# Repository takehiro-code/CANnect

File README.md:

# CANnect

Automotive diagnostic application developed as a part of engineering science 2020 capstone group croject. We built the application that diagnoses vehicle performance from On-board diagnostics-II (OBDII) port, and the mobile application displays the performance data with the Bluetooth connection from the hardware module. The dashboard on the mobile app processes the performance data and visualizes it in table, line chart, meter visualization, etc. in real-time. The performance data, which is OBDII parameter IDs (PIDs), includes engine coolant temperature, fuel pressure, engine RPM, vehicle speed, etc.

## System Overview

## Mobile App

We developed the mobile application with Android Studio, using Java and XML.

<div class="row">
  <div class="column">

  </div>
  <div class="column">

  </div>
</div>

## Contributors

- Choong Jin Ng
- Enes Yazici
- Ranjoat Chana
- Win Aung
- Nicholas Lau
- Takehiro Tanaka

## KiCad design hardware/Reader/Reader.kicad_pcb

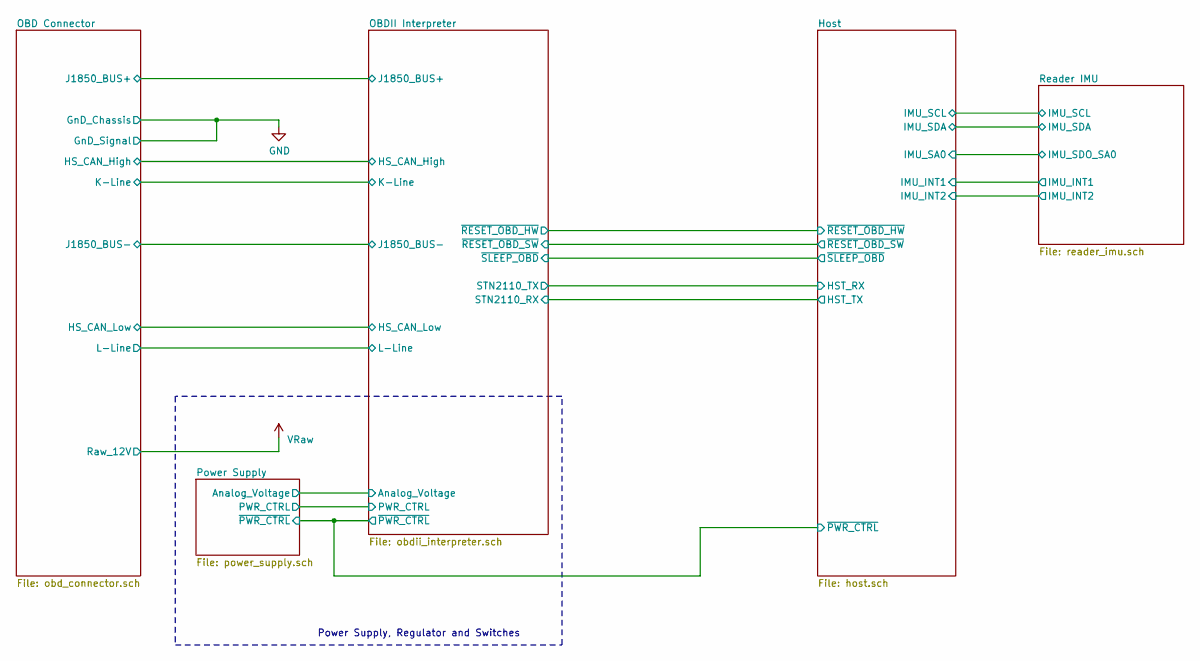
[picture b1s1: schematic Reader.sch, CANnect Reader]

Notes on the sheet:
Power Supply, Regulator and Switches

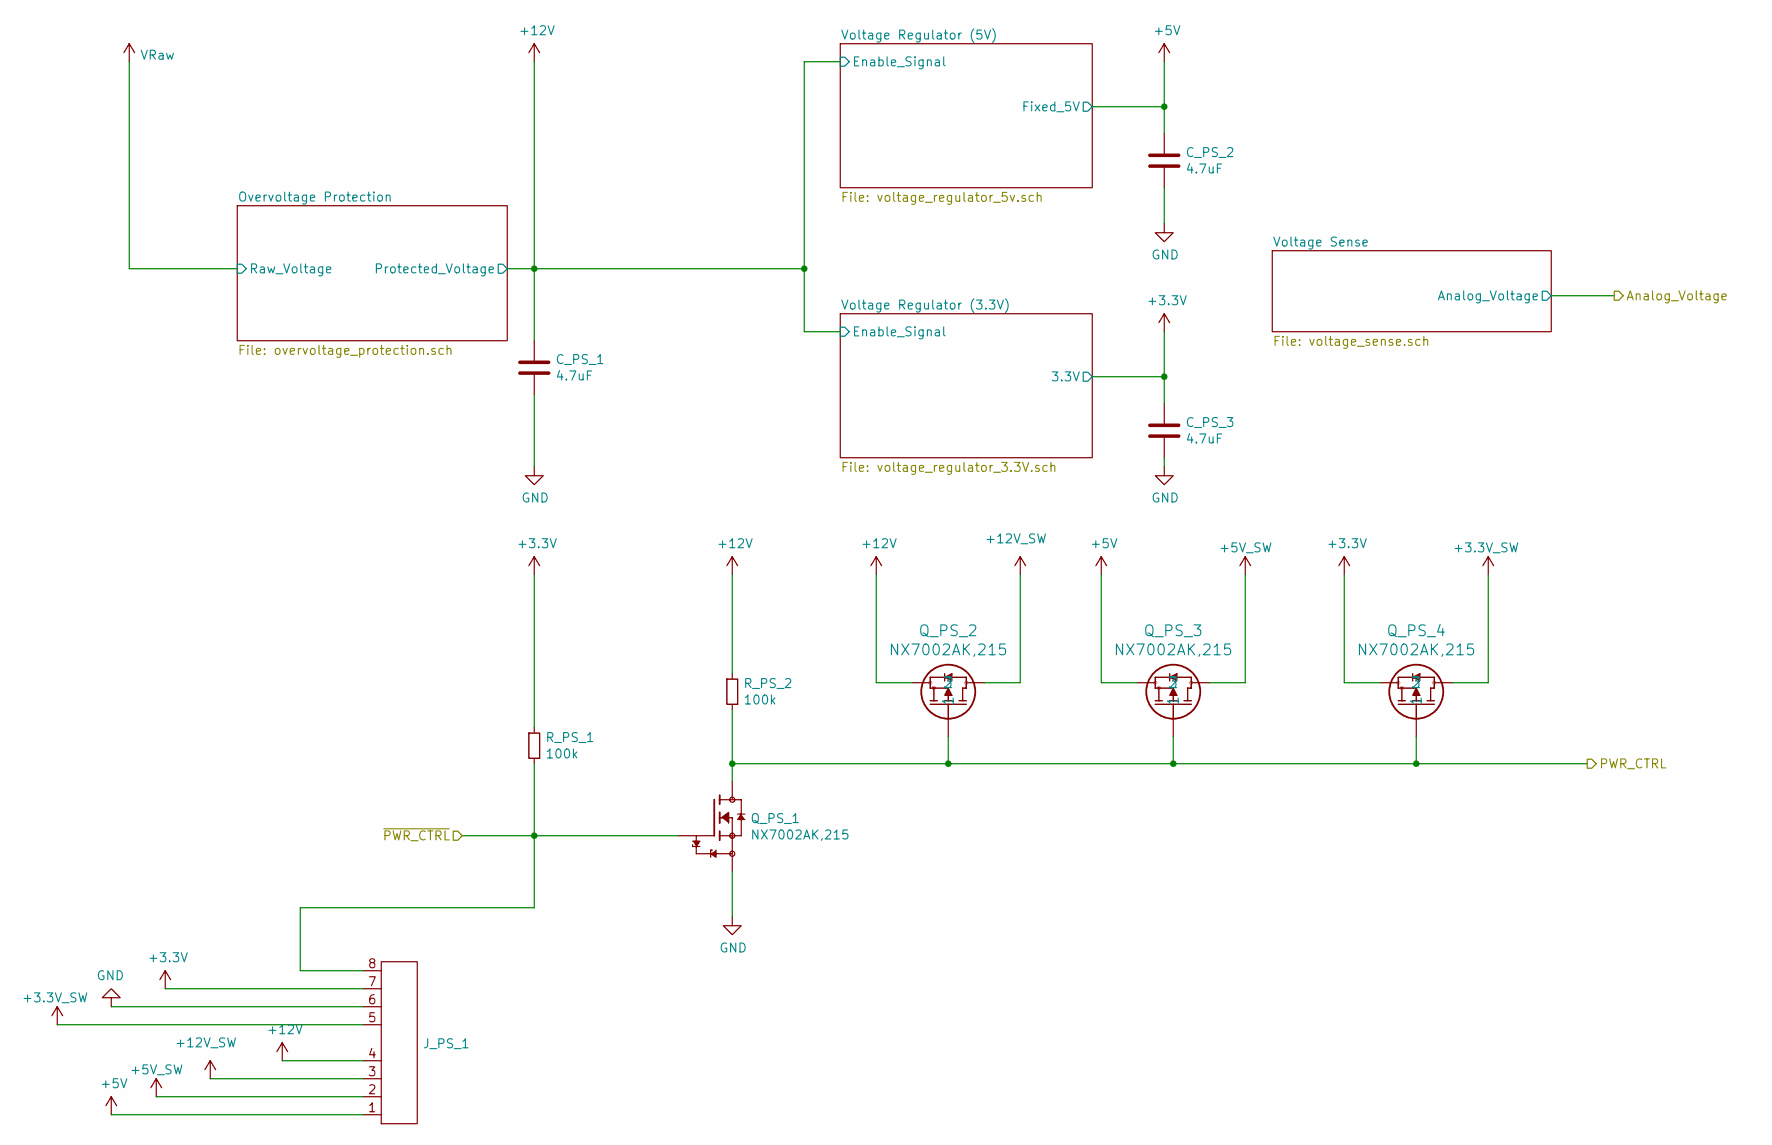
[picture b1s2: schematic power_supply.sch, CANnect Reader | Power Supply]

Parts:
C_PS_1, C_PS_2, C_PS_3: 4.7uF; C1206C475K3RACAUTO; Part Name C1206C475K3RACAUTO; digikeypn 399-7029-1-ND
J_PS_1: Header_Pin_8; PinHeader_1x08_P2.54mm_Vertical
Q_PS_1, Q_PS_2, Q_PS_3, Q_PS_4: NX7002AK,215; SOT95P230X110-3N; Part Name NX7002AK,215; digikeypn 1727-1289-1-ND
R_PS_1, R_PS_2: 100k; RESC1608X55N; Part Name RT0603DRE07100KL; digikeypn 311-2395-1-ND

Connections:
+3.3V_SW: J_PS_1.5, Q_PS_4.2
+3V3: C_PS_3.1, J_PS_1.7, Q_PS_4.3, R_PS_1.1; also elsewhere on the board
+5V: C_PS_2.1, J_PS_1.1, Q_PS_3.3; also elsewhere on the board
+5V_SW: J_PS_1.2, Q_PS_3.2; also elsewhere on the board
+12V_SW: J_PS_1.3, Q_PS_2.2; also elsewhere on the board
/Host/~PWR_CTRL~: J_PS_1.8, Q_PS_1.1, R_PS_1.2; also elsewhere on the board
/OBDII Interpreter/PWR_CTRL: Q_PS_1.3, Q_PS_2.1, Q_PS_3.1, Q_PS_4.1, R_PS_2.2; also elsewhere on the board
Pin4_GnD_Chassis: C_PS_1.2, C_PS_2.2, C_PS_3.2, J_PS_1.6, Q_PS_1.2; also elsewhere on the board

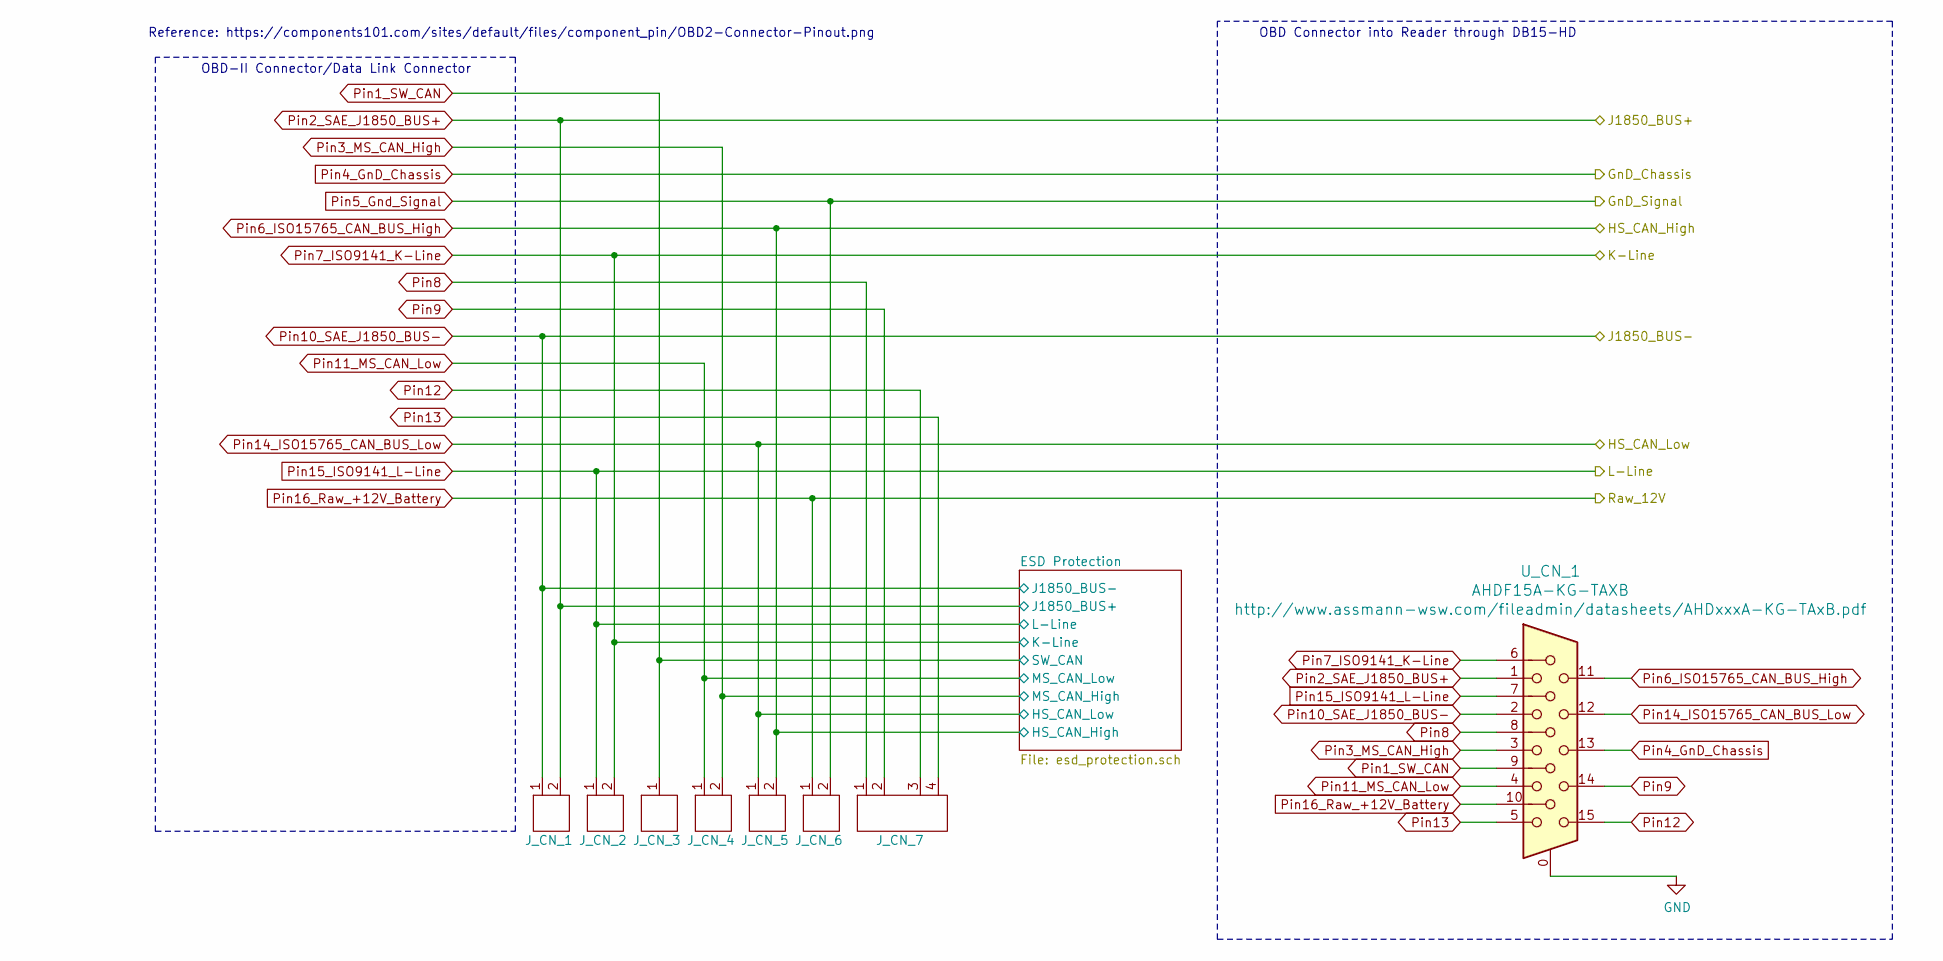
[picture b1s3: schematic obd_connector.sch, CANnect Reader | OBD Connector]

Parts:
J_CN_1, J_CN_2, J_CN_4, J_CN_5, J_CN_6: Header_Pin_2; PinHeader_1x02_P2.54mm_Vertical
J_CN_3: Header_Pin_1; PinHeader_1x01_P2.54mm_Vertical
J_CN_7: Header_Pin_4; PinHeader_1x04_P2.54mm_Vertical
U_CN_1: AHDF15A-KG-TAXB; Part Name AHDF15A-KG-TAXB; digikeypn AE11024-ND

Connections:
Pin1_SW_CAN: J_CN_3.1, U_CN_1.9; also elsewhere on the board
Pin2_SAE_J1850_BUS+: J_CN_1.2, U_CN_1.1; also elsewhere on the board
Pin3_MS_CAN_High: J_CN_4.2, U_CN_1.3; also elsewhere on the board
Pin4_GnD_Chassis: J_CN_6.2, U_CN_1.0, U_CN_1.13; also elsewhere on the board
Pin6_ISO15765_CAN_BUS_High: J_CN_5.2, U_CN_1.11; also elsewhere on the board
Pin7_ISO9141_K-Line: J_CN_2.2, U_CN_1.6; also elsewhere on the board
Pin8: J_CN_7.1, U_CN_1.8
Pin9: J_CN_7.2, U_CN_1.14
Pin10_SAE_J1850_BUS-: J_CN_1.1, U_CN_1.2; also elsewhere on the board
Pin11_MS_CAN_Low: J_CN_4.1, U_CN_1.4; also elsewhere on the board
Pin12: J_CN_7.3, U_CN_1.15
Pin13: J_CN_7.4, U_CN_1.5
Pin14_ISO15765_CAN_BUS_Low: J_CN_5.1, U_CN_1.12; also elsewhere on the board
Pin15_ISO9141_L-Line: J_CN_2.1, U_CN_1.7; also elsewhere on the board

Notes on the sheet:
OBD Connector into Reader through DB15-HD
Reference: https://components101.com/sites/default/files/component_pin/OBD2-Connector-Pinout.png
OBD-II Connector/Data Link Connector

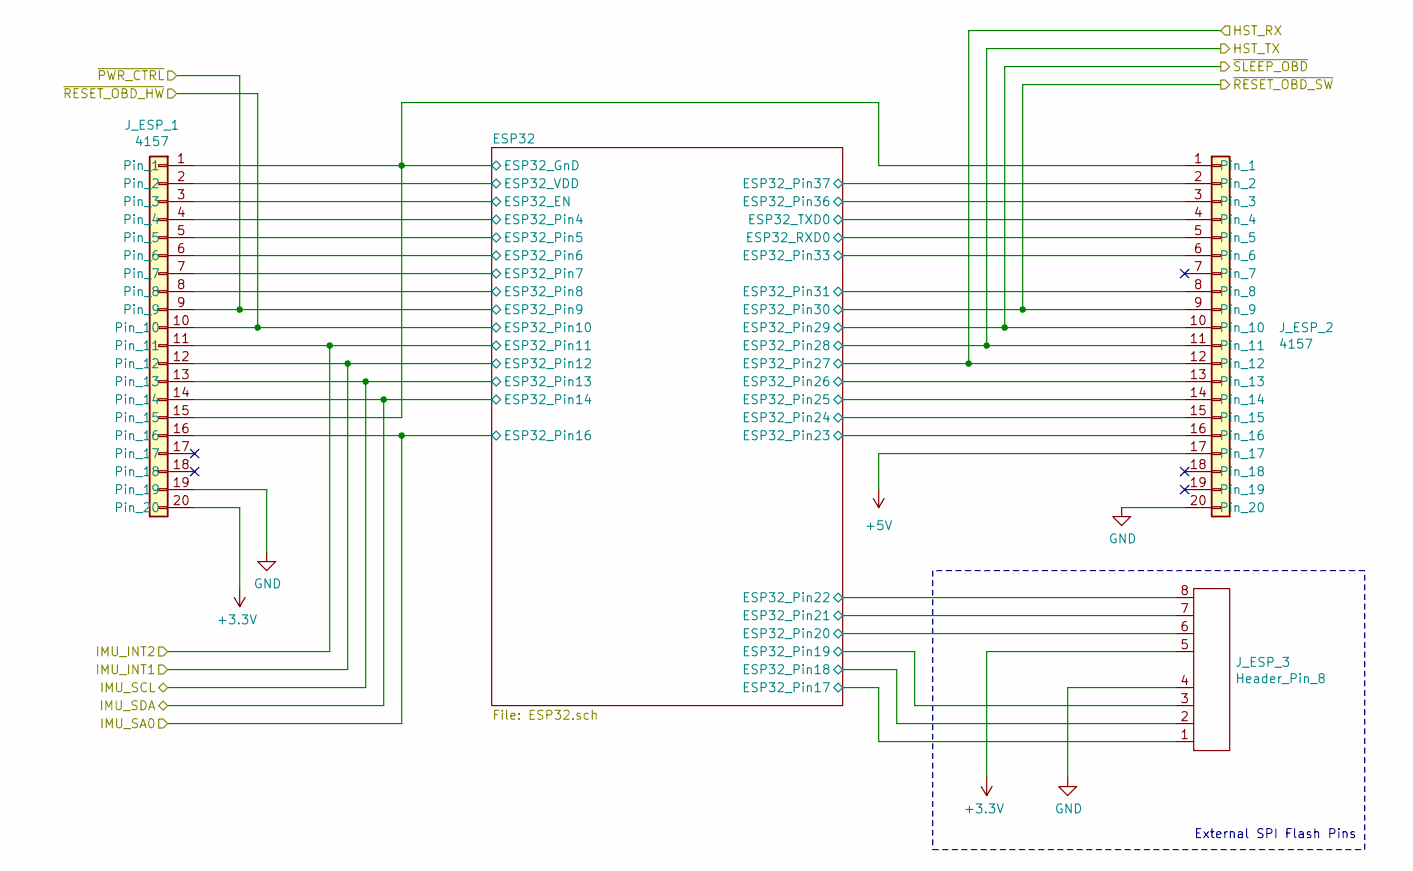
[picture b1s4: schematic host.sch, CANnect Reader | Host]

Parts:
J_ESP_1, J_ESP_2: 4157; PinSocket_1x20_P2.54mm_Vertical; Part Name 4157; digikeypn 1528-2929-ND
J_ESP_3: Header_Pin_8; PinHeader_1x08_P2.54mm_Vertical

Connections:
+3V3: J_ESP_1.2, J_ESP_1.20, J_ESP_3.5; also elsewhere on the board
+5V: J_ESP_2.17; also elsewhere on the board
/Host/ESP32/ESP32_EN: J_ESP_1.3; also elsewhere on the board
/Host/ESP32/ESP32_Pin4: J_ESP_1.4; also elsewhere on the board
/Host/ESP32/ESP32_Pin5: J_ESP_1.5; also elsewhere on the board
/Host/ESP32/ESP32_Pin6: J_ESP_1.6; also elsewhere on the board
/Host/ESP32/ESP32_Pin7: J_ESP_1.7; also elsewhere on the board
/Host/ESP32/ESP32_Pin8: J_ESP_1.8; also elsewhere on the board
/Host/ESP32/ESP32_Pin17: J_ESP_3.1; also elsewhere on the board
/Host/ESP32/ESP32_Pin18: J_ESP_3.2; also elsewhere on the board
/Host/ESP32/ESP32_Pin19: J_ESP_3.3; also elsewhere on the board
/Host/ESP32/ESP32_Pin20: J_ESP_3.6; also elsewhere on the board
/Host/ESP32/ESP32_Pin21: J_ESP_3.7; also elsewhere on the board
/Host/ESP32/ESP32_Pin22: J_ESP_3.8; also elsewhere on the board
/Host/ESP32/ESP32_Pin23: J_ESP_2.16; also elsewhere on the board
/Host/ESP32/ESP32_Pin24: J_ESP_2.15; also elsewhere on the board
/Host/ESP32/ESP32_Pin25: J_ESP_2.14; also elsewhere on the board
/Host/ESP32/ESP32_Pin26: J_ESP_2.13; also elsewhere on the board
/Host/ESP32/ESP32_Pin31: J_ESP_2.8; also elsewhere on the board
/Host/ESP32/ESP32_Pin33: J_ESP_2.6; also elsewhere on the board
/Host/ESP32/ESP32_Pin36: J_ESP_2.3; also elsewhere on the board
/Host/ESP32/ESP32_Pin37: J_ESP_2.2; also elsewhere on the board
/Host/ESP32/ESP32_RXD0: J_ESP_2.5; also elsewhere on the board
/Host/ESP32/ESP32_TXD0: J_ESP_2.4; also elsewhere on the board
/Host/HST_RX: J_ESP_2.12; also elsewhere on the board
/Host/HST_TX: J_ESP_2.11; also elsewhere on the board
/Host/IMU_INT1: J_ESP_1.12; also elsewhere on the board
/Host/IMU_INT2: J_ESP_1.11; also elsewhere on the board
/Host/IMU_SA0: J_ESP_1.16; also elsewhere on the board
/Host/IMU_SCL: J_ESP_1.13; also elsewhere on the board
/Host/IMU_SDA: J_ESP_1.14; also elsewhere on the board
/Host/~PWR_CTRL~: J_ESP_1.9; also elsewhere on the board
/Host/~RESET_OBD_HW~: J_ESP_1.10; also elsewhere on the board
/Host/~RESET_OBD_SW~: J_ESP_2.9; also elsewhere on the board
/Host/~SLEEP_OBD~: J_ESP_2.10; also elsewhere on the board
Pin4_GnD_Chassis: J_ESP_1.1, J_ESP_1.15, J_ESP_1.19, J_ESP_2.1, J_ESP_2.20, J_ESP_3.4; also elsewhere on the board

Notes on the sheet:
External SPI Flash Pins

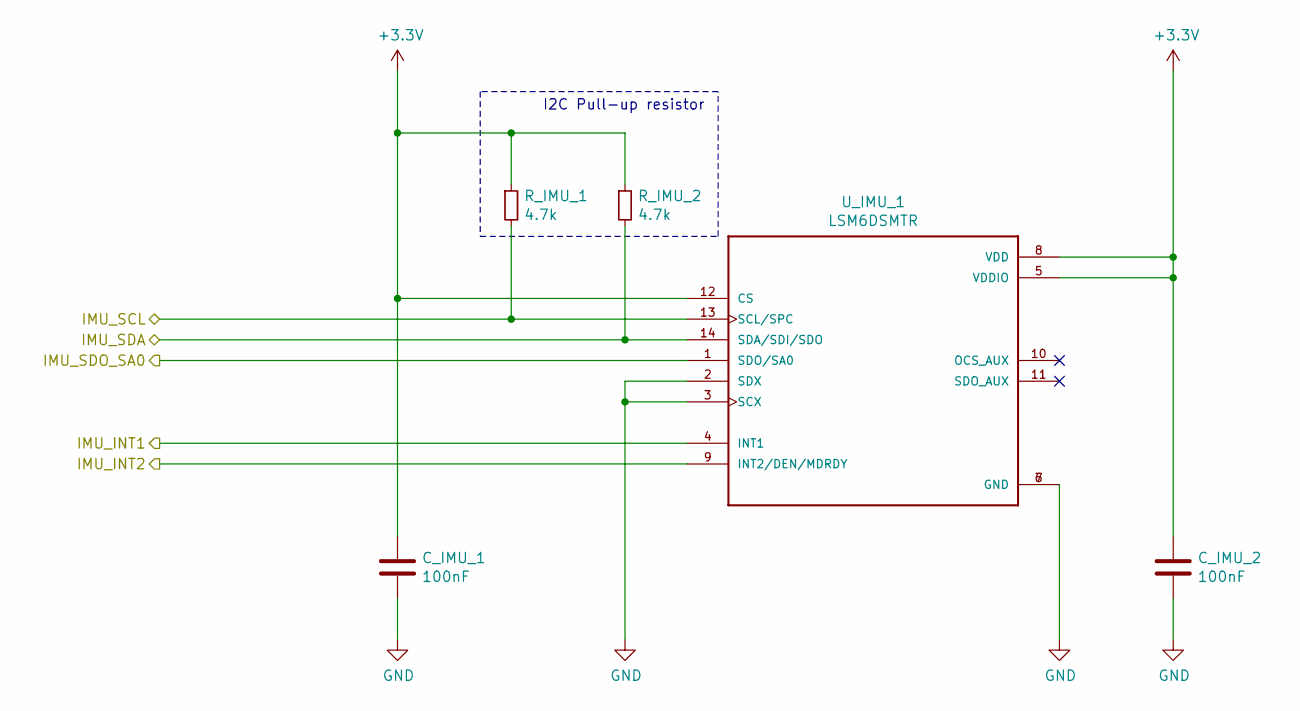
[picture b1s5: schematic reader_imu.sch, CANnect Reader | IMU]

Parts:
C_IMU_1, C_IMU_2: 100nF; CAPC1608X90N; Part Name C1608X7R2A103K080AA; digikeypn 445-1304-1-ND
R_IMU_1, R_IMU_2: 4.7k; RESC1608X55N; Part Name RT0603DRD074K7L; digikeypn 311-4.7KDCT-ND
U_IMU_1: LSM6DSMTR; PQFN50P300X250X86-14N; Part Name LSM6DSMTR; digikeypn 497-16696-1-ND

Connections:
+3V3: C_IMU_1.1, C_IMU_2.1, R_IMU_1.1, R_IMU_2.1, U_IMU_1.5 (VDDIO), U_IMU_1.8 (VDD), U_IMU_1.12 (CS); also elsewhere on the board
/Host/IMU_INT1: U_IMU_1.4 (INT1); also elsewhere on the board
/Host/IMU_INT2: U_IMU_1.9 (INT2/DEN/MDRDY); also elsewhere on the board
/Host/IMU_SA0: U_IMU_1.1 (SDO/SA0); also elsewhere on the board
/Host/IMU_SCL: R_IMU_1.2, U_IMU_1.13 (SCL/SPC); also elsewhere on the board
/Host/IMU_SDA: R_IMU_2.2, U_IMU_1.14 (SDA/SDI/SDO); also elsewhere on the board
Pin4_GnD_Chassis: C_IMU_1.2, C_IMU_2.2, U_IMU_1.2 (SDX), U_IMU_1.3 (SCX), U_IMU_1.6 (GND), U_IMU_1.7 (GND); also elsewhere on the board

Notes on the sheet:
I2C Pull-up resistor

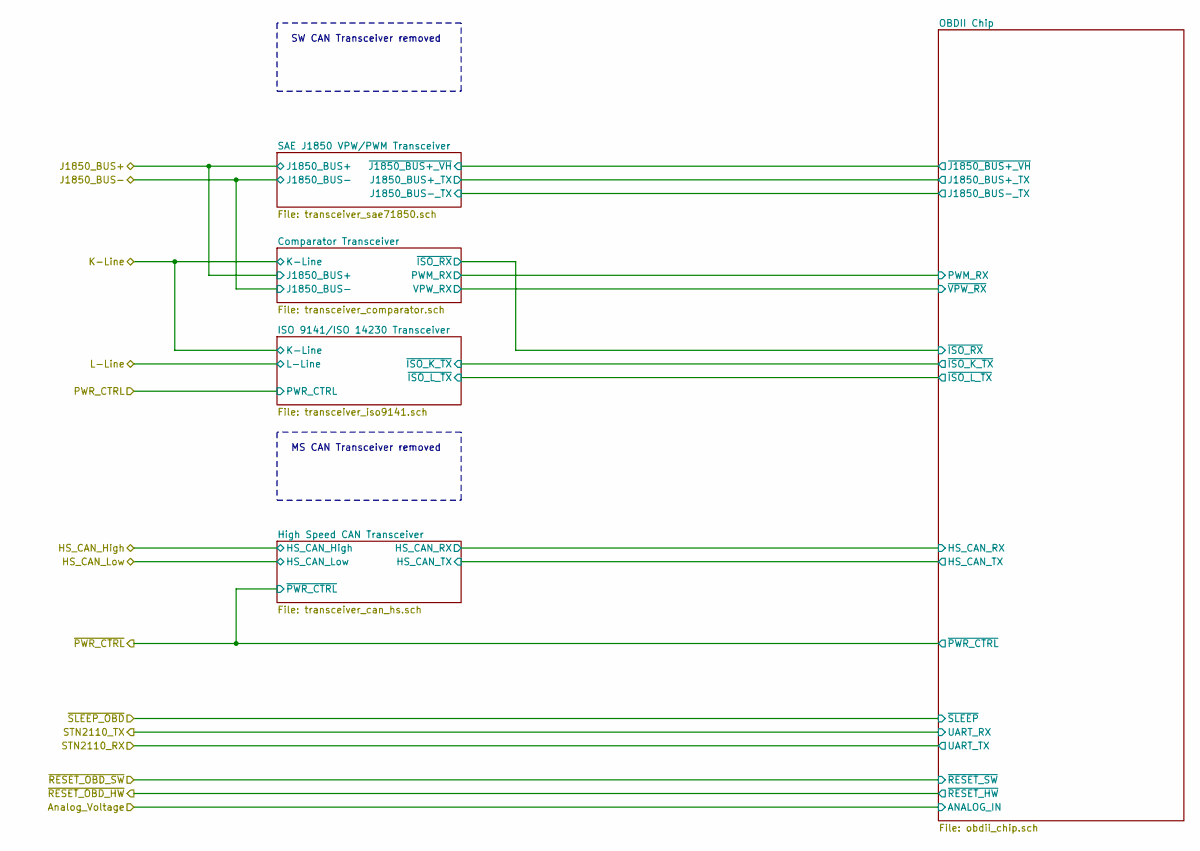
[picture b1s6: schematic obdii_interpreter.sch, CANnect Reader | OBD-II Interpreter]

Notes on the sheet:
SW CAN Transceiver removed
MS CAN Transceiver removed

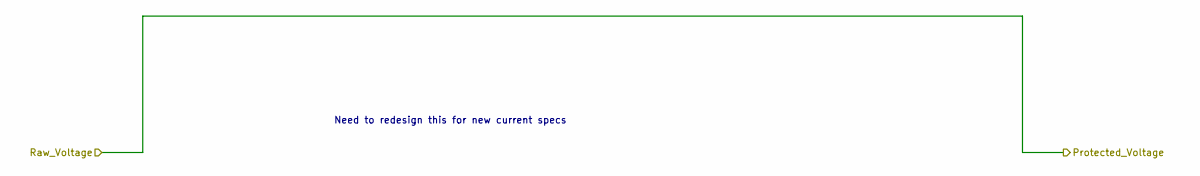
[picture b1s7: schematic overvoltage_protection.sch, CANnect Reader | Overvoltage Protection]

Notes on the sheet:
Need to redesign this for new current specs

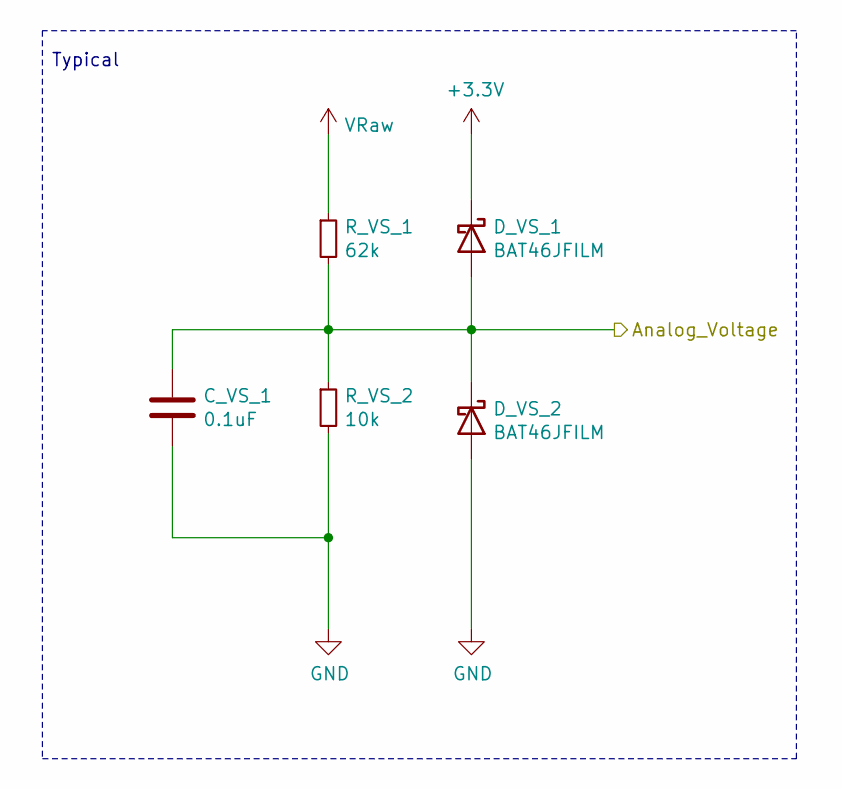
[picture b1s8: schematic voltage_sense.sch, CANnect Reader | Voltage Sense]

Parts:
C_VS_1: 0.1uF; CAPC1608X90; Part Name CC0603JRX7R8BB104; digikeypn 311-1777-1-ND
D_VS_1, D_VS_2: BAT46JFILM; Part Name BAT46JFILM; digikeypn 497-6653-1-ND
R_VS_1: 62k; RESC2012X60N; Part Name RT0805FRE0762KL; digikeypn 13-RT0805FRE0762KLCT-ND
R_VS_2: 10k; RESC1608X55N; Part Name RT0603FRE0710KL; digikeypn YAG2321CT-ND

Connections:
+3V3: D_VS_1.1 (K); also elsewhere on the board
/OBDII Interpreter/Analog_Voltage: C_VS_1.1, D_VS_1.2 (A), D_VS_2.1 (K), R_VS_1.2, R_VS_2.1; also elsewhere on the board
Pin4_GnD_Chassis: C_VS_1.2, D_VS_2.2 (A), R_VS_2.2; also elsewhere on the board

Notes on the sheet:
Typical

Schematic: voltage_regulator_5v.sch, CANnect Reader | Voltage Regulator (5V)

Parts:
C_VR1_1: 4.7uF; C1206C475K3RACAUTO; Part Name C1206C475K3RACAUTO; digikeypn 399-7029-1-ND
C_VR1_2: 0.1uF; CAPC1608X90; Part Name CC0603JRX7R8BB104; digikeypn 311-1777-1-ND
C_VR1_3: 1uF; 0603; Part Name C0603C105K4RACTU; digikeypn 399-7847-1-ND
L_VR1: 4.7uH; CV201210-4R7K; Part Name CV201210-4R7K; digikeypn CV201210-4R7KCT-ND
U_VR1: MAX25276ATCA_VY+; MAX25276ATCA&slash_VY&plus_; Part Name MAX25276ATCA/VY+; digikeypn 175-MAX25276ATCA/VY+-ND

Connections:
+5V: L_VR1.1, U_VR1.9 (OUT); also elsewhere on the board
unnamed: C_VR1_1.2, U_VR1.4 (SUP)
unnamed: C_VR1_2.1, U_VR1.3 (BST)
unnamed: C_VR1_2.2, L_VR1.2, U_VR1.5 (LX)
unnamed: C_VR1_3.1, U_VR1.8 (FB), U_VR1.10 (BIAS)
Pin4_GnD_Chassis: C_VR1_1.1, C_VR1_3.2, U_VR1.6 (PGND), U_VR1.7 (AGND), U_VR1.13 (EPAD); also elsewhere on the board

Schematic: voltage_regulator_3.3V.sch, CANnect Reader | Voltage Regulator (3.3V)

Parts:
C_VR2_1: 4.7uF; C1206C475K3RACAUTO; Part Name C1206C475K3RACAUTO; digikeypn 399-7029-1-ND
C_VR2_2: 0.1uF; CAPC1608X90; Part Name CC0603JRX7R8BB104; digikeypn 311-1777-1-ND
C_VR2_3: 1uF; 0603; Part Name C0603C105K4RACTU; digikeypn 399-7847-1-ND
L_VR2: 4.7uH; CV201210-4R7K; Part Name CV201210-4R7K; digikeypn CV201210-4R7KCT-ND
R_VR2_1, R_VR2_2: 100k; RESC1608X55N; Part Name RT0603DRE07100KL; digikeypn 311-2395-1-ND
R_VR2_3: 115k; RESC1608X55N; Part Name RT0402DRE07115KL; digikeypn 311-2218-1-ND
U_VR2: MAX25276ATCA_VY+; MAX25276ATCA&slash_VY&plus_; Part Name MAX25276ATCA/VY+; digikeypn 175-MAX25276ATCA/VY+-ND

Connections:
+3V3: L_VR2.1, R_VR2_3.1, U_VR2.9 (OUT); also elsewhere on the board
unnamed: C_VR2_1.1, U_VR2.4 (SUP)
unnamed: C_VR2_2.1, U_VR2.3 (BST)
unnamed: C_VR2_2.2, L_VR2.2, U_VR2.5 (LX)
unnamed: C_VR2_3.1, U_VR2.10 (BIAS)
unnamed: R_VR2_1.2, R_VR2_2.1, R_VR2_3.2, U_VR2.8 (FB)
Pin4_GnD_Chassis: C_VR2_1.2, C_VR2_3.2, R_VR2_1.1, R_VR2_2.2, U_VR2.6 (PGND), U_VR2.7 (AGND), U_VR2.13 (EPAD); also elsewhere on the board

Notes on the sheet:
Resistor Divider to convert 5V to 3.3V

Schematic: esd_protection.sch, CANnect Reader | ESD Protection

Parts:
D_ESD_1, D_ESD_2: PESD2CAN,215; SOT95P230X110-3N; Part Name PESD2CAN,215; digikeypn 1727-3891-1-ND
D_ESD_3: MMBZ27VCLFHT116; Part Name MMBZ27VCLFHT116; digikeypn MMBZ27VCLFHT116CT-ND
D_ESD_4, D_ESD_5: MMBZ27VALT3G; SOT95P237X111-3N; Part Name MMBZ27VALT3G; digikeypn MMBZ27VALT3GOSCT-ND

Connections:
Pin1_SW_CAN: D_ESD_3.2; also elsewhere on the board
Pin2_SAE_J1850_BUS+: D_ESD_5.1; also elsewhere on the board
Pin3_MS_CAN_High: D_ESD_2.1; also elsewhere on the board
Pin4_GnD_Chassis: D_ESD_1.3, D_ESD_2.3, D_ESD_3.1, D_ESD_4.3, D_ESD_5.3; also elsewhere on the board
Pin6_ISO15765_CAN_BUS_High: D_ESD_1.1; also elsewhere on the board
Pin7_ISO9141_K-Line: D_ESD_4.1; also elsewhere on the board
Pin10_SAE_J1850_BUS-: D_ESD_5.2; also elsewhere on the board
Pin11_MS_CAN_Low: D_ESD_2.2; also elsewhere on the board
Pin14_ISO15765_CAN_BUS_Low: D_ESD_1.2; also elsewhere on the board
Pin15_ISO9141_L-Line: D_ESD_4.2; also elsewhere on the board

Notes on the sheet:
ESD Protection (IEC61000-4-2 Level 4)

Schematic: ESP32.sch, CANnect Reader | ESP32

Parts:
CP_ESP_1: 100uF; UCB0J101MCL1GS; Part Name UCB0J101MCL1GS; digikeypn 493-9357-1-ND
C_ESP_1, C_ESP_2: 0.1uF; CAPC1608X90; Part Name CC0603JRX7R8BB104; digikeypn 311-1777-1-ND
LED_ESP_1: Bluetooth Status; LED_0603_1608Metric; Part Name 150060VS75000; digikeypn 732-4980-1-ND
R_ESP_1, R_ESP_4: 10k; RESC1608X55N; Part Name RT0603FRE0710KL; digikeypn YAG2321CT-ND
R_ESP_2, R_ESP_3, R_ESP_5: 500; RESC1508X55N; Part Name MCT0603PD4990DP500; digikeypn 749-1523-1-ND
SW_ESP_1, SW_ESP_2: PTS647SK38SMTR2LFS; Part Name PTS 647 SK38 SMTR2 LFS; digikeypn PTS647SK38SMTR2LFSCT-ND
U_ESP_1: ESP32-WROOM-32D; CANtech-ESP32-WROOM-32; Part Name USB4110-GF-A; digikeypn 1965-ESP32-WROOM-32D(4MB)CT-ND

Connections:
+3V3: CP_ESP_1.1, R_ESP_1.1, R_ESP_4.2, U_ESP_1.2 (VDD); also elsewhere on the board
/Host/ESP32/ESP32_EN: C_ESP_1.1, SW_ESP_1.2, U_ESP_1.3 (EN); also elsewhere on the board
/Host/ESP32/ESP32_Pin4: U_ESP_1.4 (SENSOR_VP); also elsewhere on the board
/Host/ESP32/ESP32_Pin5: U_ESP_1.5 (SENSOR_VN); also elsewhere on the board
/Host/ESP32/ESP32_Pin6: U_ESP_1.6 (IO34); also elsewhere on the board
/Host/ESP32/ESP32_Pin7: U_ESP_1.7 (IO35); also elsewhere on the board
/Host/ESP32/ESP32_Pin8: U_ESP_1.8 (IO32); also elsewhere on the board
/Host/ESP32/ESP32_Pin17: U_ESP_1.17 (SHD/SD2); also elsewhere on the board
/Host/ESP32/ESP32_Pin18: U_ESP_1.18 (SWP/SD3); also elsewhere on the board
/Host/ESP32/ESP32_Pin19: U_ESP_1.19 (SCS/CMD); also elsewhere on the board
/Host/ESP32/ESP32_Pin20: U_ESP_1.20 (SCK/CLK); also elsewhere on the board
/Host/ESP32/ESP32_Pin21: U_ESP_1.21 (SDO/SD0); also elsewhere on the board
/Host/ESP32/ESP32_Pin22: U_ESP_1.22 (SDI/SD1); also elsewhere on the board
/Host/ESP32/ESP32_Pin23: U_ESP_1.23 (IO15); also elsewhere on the board
/Host/ESP32/ESP32_Pin24: R_ESP_3.2, U_ESP_1.24 (IO2); also elsewhere on the board
/Host/ESP32/ESP32_Pin25: C_ESP_2.1, SW_ESP_2.3, U_ESP_1.25 (IO0); also elsewhere on the board
/Host/ESP32/ESP32_Pin26: U_ESP_1.26 (IO4); also elsewhere on the board
/Host/ESP32/ESP32_Pin31: U_ESP_1.31 (IO19); also elsewhere on the board
/Host/ESP32/ESP32_Pin33: U_ESP_1.33 (IO21); also elsewhere on the board
/Host/ESP32/ESP32_Pin36: U_ESP_1.36 (IO22); also elsewhere on the board
/Host/ESP32/ESP32_Pin37: U_ESP_1.37 (IO23); also elsewhere on the board
/Host/ESP32/ESP32_RXD0: U_ESP_1.34 (RXD0/IO3); also elsewhere on the board
/Host/ESP32/ESP32_TXD0: U_ESP_1.35 (TXD0/IO1); also elsewhere on the board
/Host/HST_RX: U_ESP_1.27 (IO16); also elsewhere on the board
/Host/HST_TX: U_ESP_1.28 (IO17); also elsewhere on the board
/Host/IMU_INT1: U_ESP_1.12 (IO27); also elsewhere on the board
/Host/IMU_INT2: U_ESP_1.11 (IO26); also elsewhere on the board
/Host/IMU_SA0: U_ESP_1.16 (IO13); also elsewhere on the board
/Host/IMU_SCL: U_ESP_1.13 (IO14); also elsewhere on the board
/Host/IMU_SDA: U_ESP_1.14 (IO12); also elsewhere on the board
/Host/~PWR_CTRL~: U_ESP_1.9 (IO33); also elsewhere on the board
/Host/~RESET_OBD_HW~: U_ESP_1.10 (IO25); also elsewhere on the board
/Host/~RESET_OBD_SW~: U_ESP_1.30 (IO18); also elsewhere on the board
/Host/~SLEEP_OBD~: U_ESP_1.29 (IO5); also elsewhere on the board
unnamed: LED_ESP_1.2 (A), R_ESP_3.1
unnamed: R_ESP_1.2, SW_ESP_1.1
unnamed: R_ESP_2.1, SW_ESP_1.3
unnamed: R_ESP_4.1, SW_ESP_2.2
unnamed: R_ESP_5.2, SW_ESP_2.4
Pin4_GnD_Chassis: CP_ESP_1.2, C_ESP_1.2, C_ESP_2.2, LED_ESP_1.1 (K), R_ESP_2.2, R_ESP_5.1, U_ESP_1.1 (GND), U_ESP_1.15 (GND), U_ESP_1.38 (GND), U_ESP_1.39 (GND); also elsewhere on the board

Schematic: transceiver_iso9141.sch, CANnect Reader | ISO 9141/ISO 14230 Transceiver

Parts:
Q_ISO_1, Q_ISO_2: IRLML5103TRPBF; Part Name IRLML5103TRPBF; digikeypn IRLML5103PBFCT-ND
Q_ISO_3, Q_ISO_4: MMBT3904WT1G; SOT-23; Part Name MMBT3904WT1G; digikeypn MMBT3904WT1GOSCT-ND
R_ISO_1, R_ISO_2: 1k; RC1608F102CS; Part Name RC1608F102CS; digikeypn 1276-3484-1-ND
R_ISO_3, R_ISO_4: 510k; RESC2012X50N; Part Name RR1220P-514-D; digikeypn RR12P510KDCT-ND

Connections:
/OBDII Interpreter/ISO 9141/ISO 14230 Transceiver/~ISO_K_TX~: R_ISO_1.2; also elsewhere on the board
/OBDII Interpreter/ISO 9141/ISO 14230 Transceiver/~ISO_L_TX~: R_ISO_2.2; also elsewhere on the board
/OBDII Interpreter/PWR_CTRL: Q_ISO_1.1, Q_ISO_2.1; also elsewhere on the board
unnamed: Q_ISO_1.2, R_ISO_3.2
unnamed: Q_ISO_2.2, R_ISO_4.2
unnamed: Q_ISO_3.1 (B), R_ISO_1.1
unnamed: Q_ISO_4.1 (B), R_ISO_2.1
Pin4_GnD_Chassis: Q_ISO_3.2 (E), Q_ISO_4.2 (E); also elsewhere on the board
Pin7_ISO9141_K-Line: Q_ISO_3.3 (C), R_ISO_3.1; also elsewhere on the board
Pin15_ISO9141_L-Line: Q_ISO_4.3 (C), R_ISO_4.1; also elsewhere on the board

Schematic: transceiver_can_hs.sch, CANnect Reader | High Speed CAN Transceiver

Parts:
C_HSCAN_1, C_HSCAN_2: 560pF; CAPC1608X90; Part Name CC0603JRX7R9BB561; digikeypn 311-4020-1-ND‎
C_HSCAN_3: 1uF; 0603; Part Name C0603C105K4RACTU; digikeypn 399-7847-1-ND
Q_HSCAN_1: NX7002AK,215; SOT95P230X110-3N; Part Name NX7002AK,215; digikeypn 1727-1289-1-ND
R_HSCAN_1: 100k; RESC1608X55N; Part Name RT0603DRE07100KL; digikeypn 311-2395-1-ND
R_HSCAN_2, R_HSCAN_3: 100; RESC3216X70N; Part Name ERJ-8ENF1000V; digikeypn P100FCT-ND
U_HSCAN_1: MCP2562-H_MF; MCP2562-H&slash_MF; Part Name MCP2562-H_MF; digikeypn MCP2562-H/MF-ND

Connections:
+3V3: R_HSCAN_1.1, U_HSCAN_1.5 (VIO); also elsewhere on the board
+5V: C_HSCAN_3.2, U_HSCAN_1.3 (VDD); also elsewhere on the board
/Host/~PWR_CTRL~: Q_HSCAN_1.1; also elsewhere on the board
/OBDII Interpreter/High Speed CAN Transceiver/HS_CAN_RX: U_HSCAN_1.4 (RXD); also elsewhere on the board
/OBDII Interpreter/High Speed CAN Transceiver/HS_CAN_TX: U_HSCAN_1.1 (TXD); also elsewhere on the board
unnamed: C_HSCAN_1.1, R_HSCAN_2.2
unnamed: C_HSCAN_2.1, R_HSCAN_3.2
unnamed: Q_HSCAN_1.3, R_HSCAN_1.2, U_HSCAN_1.8 (STBY)
Pin4_GnD_Chassis: C_HSCAN_1.2, C_HSCAN_2.2, C_HSCAN_3.1, Q_HSCAN_1.2, U_HSCAN_1.2 (VSS), U_HSCAN_1.9 (EPAD); also elsewhere on the board
Pin6_ISO15765_CAN_BUS_High: R_HSCAN_3.1, U_HSCAN_1.7 (CANH); also elsewhere on the board
Pin14_ISO15765_CAN_BUS_Low: R_HSCAN_2.1, U_HSCAN_1.6 (CANL); also elsewhere on the board

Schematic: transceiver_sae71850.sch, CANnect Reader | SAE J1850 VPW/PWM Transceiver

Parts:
C_J1850_1: 0.1uF; CAPC1608X90; Part Name CC0603JRX7R8BB104; digikeypn 311-1777-1-ND
D_J1850_1, D_J1850_2, D_J1850_3: BAT46JFILM; Part Name BAT46JFILM; digikeypn 497-6653-1-ND
Q_J1850_1, Q_J1850_2, Q_J1850_4: NX7002AK,215; SOT95P230X110-3N; Part Name NX7002AK,215; digikeypn 1727-1289-1-ND
Q_J1850_3: RSC002P03T316; Part Name RSC002P03T316; digikeypn RSC002P03T316CT-ND
R_J1850_1, R_J1850_5, R_J1850_7, R_J1850_8: 10k; RESC1608X55N; Part Name RT0603FRE0710KL; digikeypn YAG2321CT-ND
R_J1850_2: 1.5k; RESC1607X60N; Part Name RC0603FR-071K5L; digikeypn 311-1.50KHRCT-ND
R_J1850_3: 866; RESC3216X70N; Part Name ERJ-8ENF8660V; digikeypn P866FCT-ND
R_J1850_4: 374; RESC3216X70N; Part Name ERJ-8ENF3740V; digikeypn P374FCT-ND
R_J1850_6: 240; RESC3216X70N; Part Name ERJ-8ENF2400V; digikeypn P240FCT-ND
U_J1850_1: LM317LDR2G; SOIC127P600X175-8N; Part Name LM317LDR2G; digikeypn LM317LDR2GOSCT-ND

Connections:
+5V_SW: D_J1850_3.2 (A); also elsewhere on the board
+V_J1850: Q_J1850_3.2, R_J1850_2.1, R_J1850_6.1, U_J1850_1.2 (VOUT)
/OBDII Interpreter/OBDII Chip/J1850_BUS+_TX: Q_J1850_2.1, R_J1850_1.1; also elsewhere on the board
/OBDII Interpreter/OBDII Chip/J1850_BUS-_TX: Q_J1850_4.1, R_J1850_7.1; also elsewhere on the board
/OBDII Interpreter/OBDII Chip/~J1850_BUS+_VH~: Q_J1850_1.1; also elsewhere on the board
unnamed: C_J1850_1.1, U_J1850_1.1 (VIN)
unnamed: D_J1850_1.2 (A), Q_J1850_3.3
unnamed: D_J1850_2.2 (A), R_J1850_5.2
unnamed: D_J1850_3.1 (K), R_J1850_8.1
unnamed: Q_J1850_1.3, R_J1850_3.1, R_J1850_4.1
unnamed: Q_J1850_2.3, Q_J1850_3.1, R_J1850_2.2
unnamed: R_J1850_3.2, R_J1850_6.2, U_J1850_1.4 (ADJUST)
Pin2_SAE_J1850_BUS+: D_J1850_1.1 (K), R_J1850_5.1; also elsewhere on the board
Pin4_GnD_Chassis: C_J1850_1.2, D_J1850_2.1 (K), Q_J1850_1.2, Q_J1850_2.2, Q_J1850_4.2, R_J1850_1.2, R_J1850_4.2, R_J1850_7.2; also elsewhere on the board
Pin10_SAE_J1850_BUS-: Q_J1850_4.3, R_J1850_8.2; also elsewhere on the board

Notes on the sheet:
SAE J1850 Power Supply for WM (5V) and VPW (7V)
J1850 BUS+ Transmitter
J1850 BUS- Transmitter

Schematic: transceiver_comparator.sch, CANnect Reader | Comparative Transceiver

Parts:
R_COMP_1, R_COMP_2, R_COMP_3, R_COMP_4, R_COMP_5, R_COMP_6, R_COMP_7, R_COMP_9, R_COMP_10, R_COMP_11: 10k; RESC1608X55N; Part Name RT0603FRE0710KL; digikeypn YAG2321CT-ND
R_COMP_8: 2.7k; RESC1608X55N; Part Name CRCW06032K70FKEAC; digikeypn 541-5328-1-ND
U_COMP_1: LM339N_NOPB; LM339N&slash_NOPB; Part Name LM339N_NOPB; digikeypn 296-39010-5-ND

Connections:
+3V3: R_COMP_4.1, R_COMP_5.1, R_COMP_11.1; also elsewhere on the board
+5V_SW: R_COMP_8.1; also elsewhere on the board
+12V_SW: R_COMP_6.1, U_COMP_1.3 (VCC); also elsewhere on the board
/OBDII Interpreter/Comparator Transceiver/PWM_RX: R_COMP_4.2, U_COMP_1.2 (2OUT); also elsewhere on the board
/OBDII Interpreter/Comparator Transceiver/VPW_RX: R_COMP_11.2, U_COMP_1.14 (OUT3); also elsewhere on the board
/OBDII Interpreter/Comparator Transceiver/~ISO_RX~: R_COMP_5.2, U_COMP_1.1 (1OUT); also elsewhere on the board
unnamed: R_COMP_1.2, U_COMP_1.5 (2IN+)
unnamed: R_COMP_2.2, U_COMP_1.6 (1IN-)
unnamed: R_COMP_3.1, U_COMP_1.4 (2IN-)
unnamed: R_COMP_6.2, R_COMP_7.1, U_COMP_1.7 (1IN+)
unnamed: R_COMP_8.2, R_COMP_9.1, U_COMP_1.8 (3IN-)
unnamed: R_COMP_10.1, U_COMP_1.9 (3IN+)
Pin2_SAE_J1850_BUS+: R_COMP_1.1, R_COMP_10.2; also elsewhere on the board
Pin4_GnD_Chassis: R_COMP_7.2, R_COMP_9.2, U_COMP_1.12 (GND); also elsewhere on the board
Pin7_ISO9141_K-Line: R_COMP_2.1; also elsewhere on the board
Pin10_SAE_J1850_BUS-: R_COMP_3.2; also elsewhere on the board

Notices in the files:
parts and their libraries:
Copyright 2016 Accelerated Designs. All rights reserved.
